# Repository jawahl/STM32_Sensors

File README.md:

# STM32_Sensors
Designing a board around the STM32F407 microcontroller to interface with GPS Rx, IMU, Temp sensors. 
Goal is to implement data logging & data filtering (dsp/control algorithms) in C/C++ firmware. 
Would also like to familiarize myself with freeRTOS.

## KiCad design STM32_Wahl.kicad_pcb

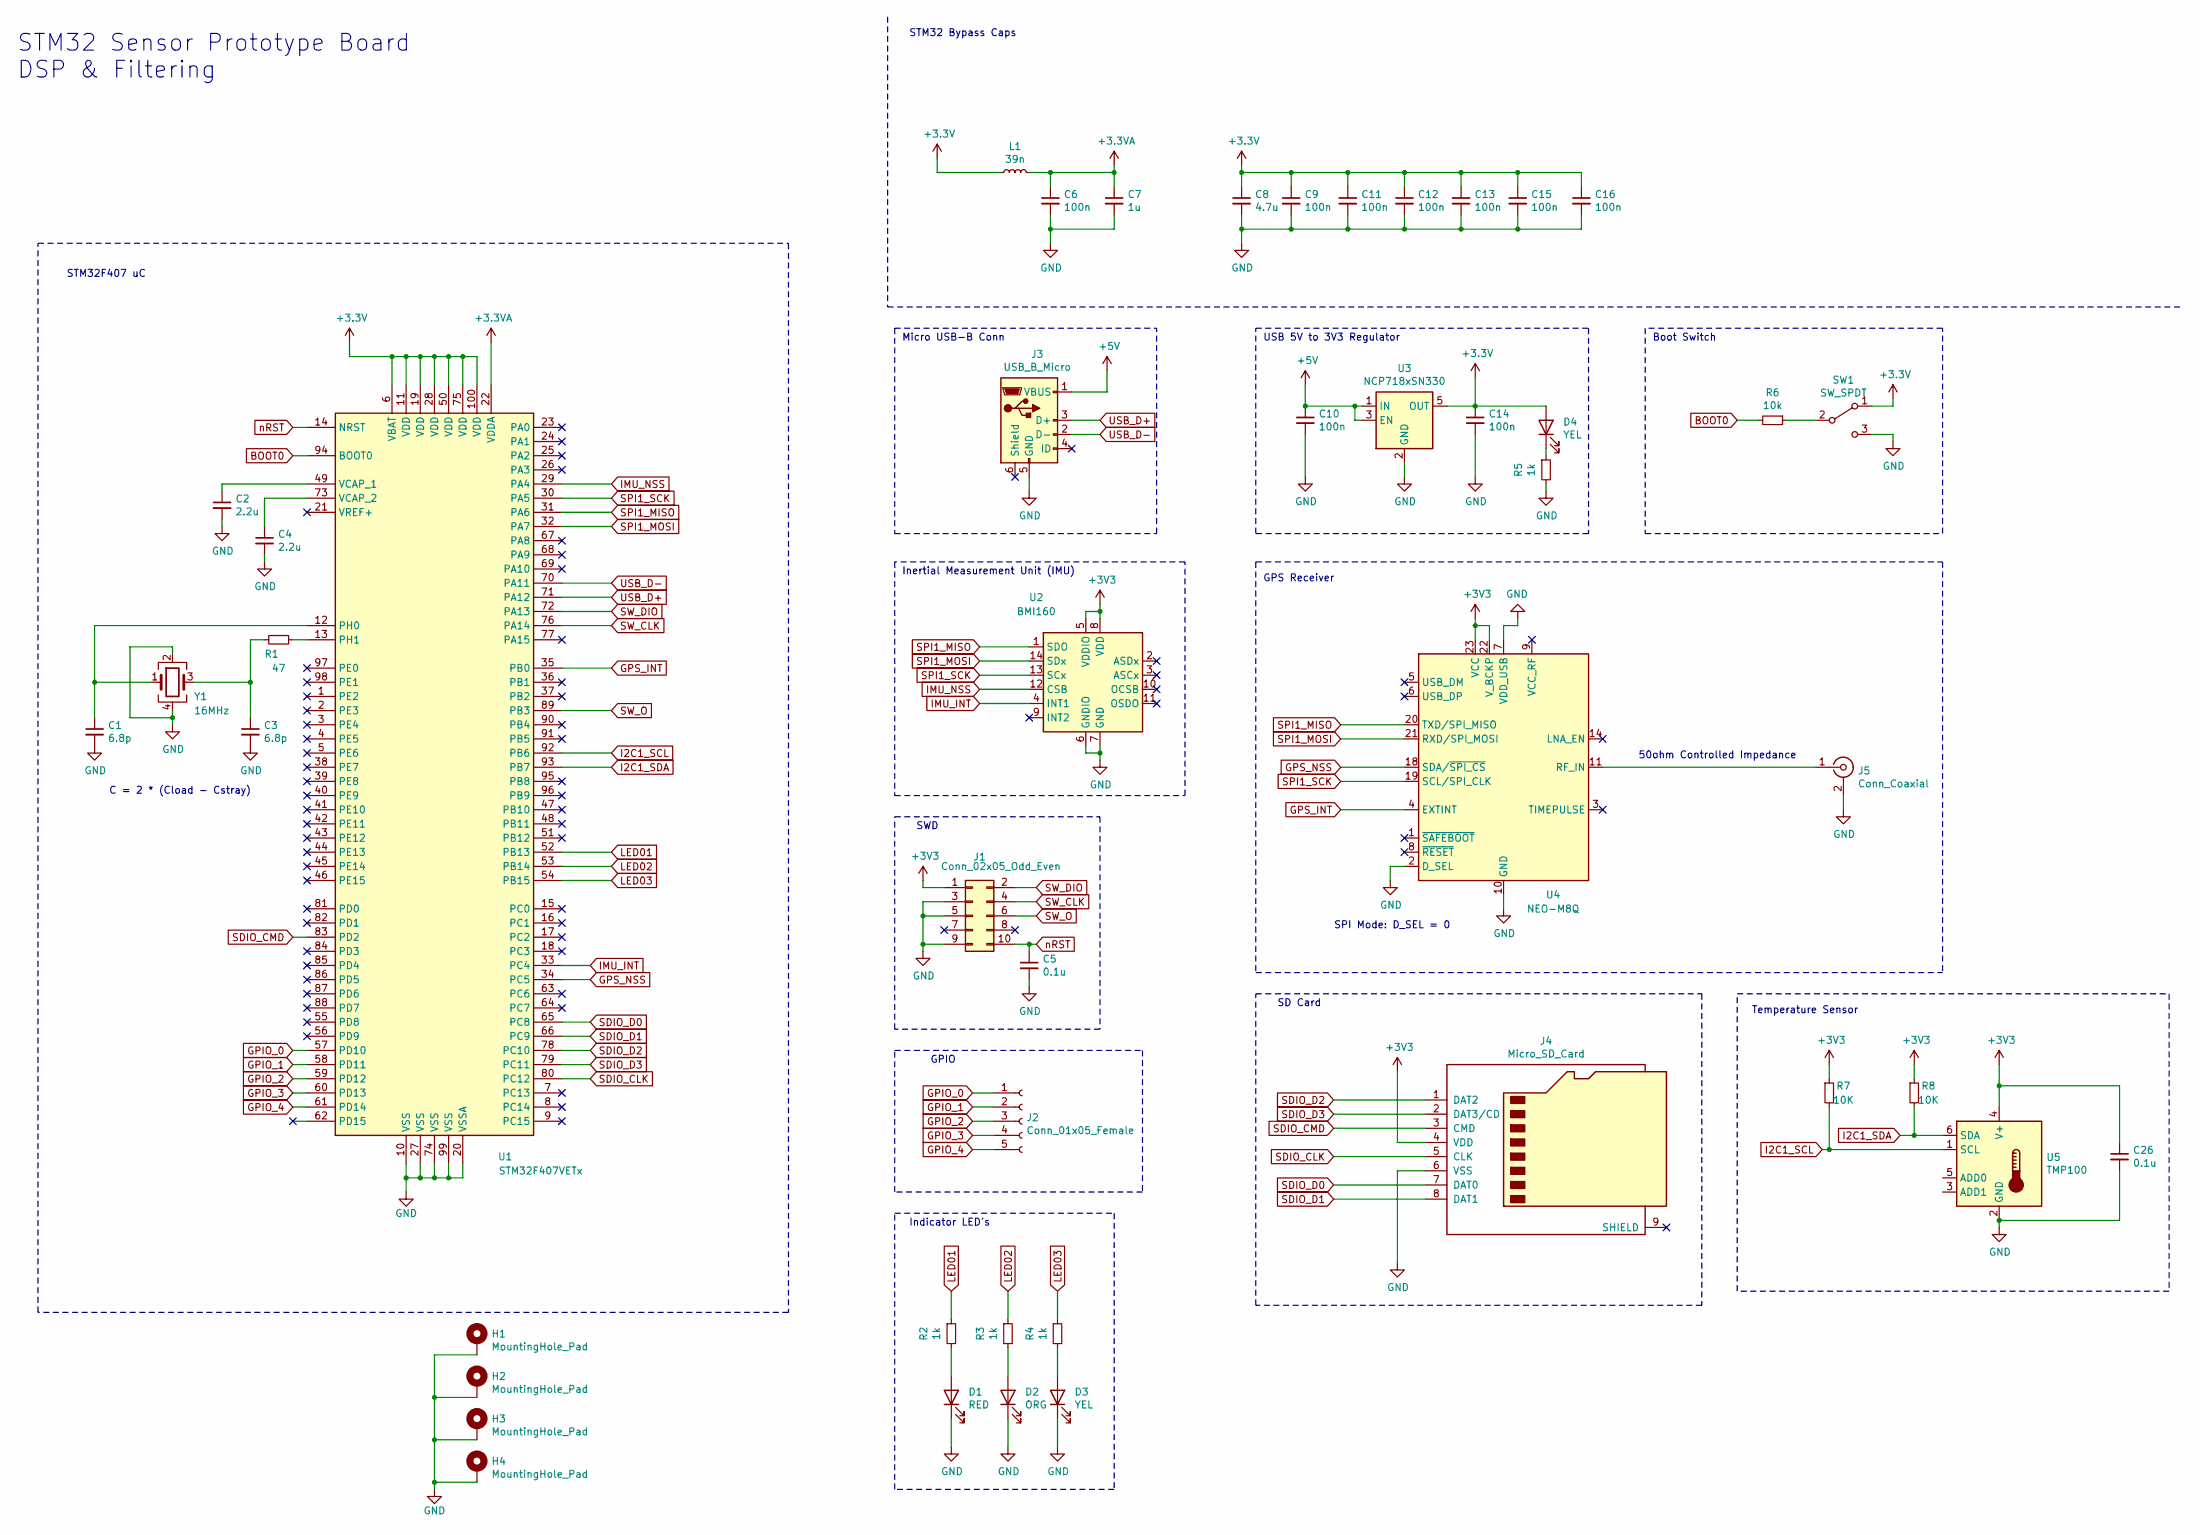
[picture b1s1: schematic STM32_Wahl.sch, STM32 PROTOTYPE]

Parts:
C1, C3: 6.8p; C_0402_1005Metric
C2, C4: 2.2u; C_0603_1608Metric
C5, C26: 0.1u; C_0603_1608Metric
C6: 100n; C_0603_1608Metric
C7: 1u; C_0603_1608Metric
C8: 4.7u; C_0603_1608Metric
C9, C10, C11, C12, C13, C14, C15, C16: 100n; C_0402_1005Metric
D1: RED; LED_0603_1608Metric
D2: ORG; LED_0603_1608Metric
D3, D4: YEL; LED_0603_1608Metric
H1, H2, H3, H4: MountingHole_Pad; MountingHole_4.3mm_M4_Pad_Via
J1: Conn_02x05_Odd_Even; PinHeader_2x05_P1.27mm_Vertical_SMD
J2: Conn_01x05_Female; PinSocket_1x05_P1.27mm_Vertical_SMD_Pin1Left
J3: USB_B_Micro; USB_Micro-B_Amphenol_10118194_Horizontal
J4: Micro_SD_Card; microSD_HC_Molex_104031-0811
J5: Conn_Coaxial; SMA_Amphenol_132291_Vertical
L1: 39n; L_0402_1005Metric
R1: 47; R_0402_1005Metric
R2, R3, R4, R5: 1k; R_0603_1608Metric
R6: 10k; R_0402_1005Metric
R7, R8: 10K; R_0402_1005Metric
SW1: SW_SPDT; SW_SPDT_PCM12
U1: STM32F407VETx; LQFP-100_14x14mm_P0.5mm
U2: BMI160; Bosch_LGA-14_3x2.5mm_P0.5mm
U3: NCP718xSN330; SOT-23-5
U4: NEO-M8Q; ublox_NEO
U5: TMP100; SOT-23-6
Y1: 16MHz; Crystal_SMD_3225-4Pin_3.2x2.5mm

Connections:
+3.3VA: C6.1, C7.1, L1.2, U1.22 (VDDA)
+5V: C10.1, J3.1 (VBUS), U3.1 (IN), U3.3 (EN)
BOOT0: R6.2, U1.94 (BOOT0)
GND: C1.2, C2.2, C3.2, C4.2, C5.2, C6.2, C7.2, C8.2, C9.2, C10.2, C11.2, C12.2, C13.2, C14.2, C15.2, C16.2, C26.2, D1.1 (K), D2.1 (K), D3.1 (K), H1.1, H2.1, H3.1, H4.1, J1.3, J1.5, J1.9, J3.5 (GND), J4.6 (VSS), J5.2 (Ext), R5.2, SW1.3 (C), U1.10 (VSS), U1.20 (VSSA), U1.27 (VSS), U1.74 (VSS), U1.99 (VSS), U2.6 (GNDIO), U2.7 (GND), U3.2 (GND), U4.2 (D_SEL), U4.7 (VDD_USB), U4.10 (GND), U4.12 (GND), U4.13 (GND), U4.24 (GND), U5.2 (GND), Y1.2, Y1.4
GPIO_0: J2.1, U1.57 (PD10)
GPIO_1: J2.2, U1.58 (PD11)
GPIO_2: J2.3, U1.59 (PD12)
GPIO_3: J2.4, U1.60 (PD13)
GPIO_4: J2.5, U1.61 (PD14)
GPS_INT: U1.35 (PB0), U4.4 (EXTINT)
GPS_NSS: U1.34 (PC5), U4.18 (SDA/~SPI_CS)
I2C1_SCL: R7.2, U1.92 (PB6), U5.1 (SCL)
I2C1_SDA: R8.2, U1.93 (PB7), U5.6 (SDA)
IMU_INT: U1.33 (PC4), U2.4 (INT1)
IMU_NSS: U1.29 (PA4), U2.12 (CSB)
LED01: R2.1, U1.52 (PB13)
LED02: R3.1, U1.53 (PB14)
LED03: R4.1, U1.54 (PB15)
unnamed: C1.1, U1.12 (PH0), Y1.1
unnamed: C2.1, U1.49 (VCAP_1)
unnamed: C3.1, R1.2, Y1.3
unnamed: C4.1, U1.73 (VCAP_2)
unnamed: D1.2 (A), R2.2
unnamed: D2.2 (A), R3.2
unnamed: D3.2 (A), R4.2
unnamed: D4.1 (K), R5.1
unnamed: J5.1 (In), U4.11 (RF_IN)
unnamed: R1.1, U1.13 (PH1)
unnamed: R6.1, SW1.2 (B)
SDIO_CLK: J4.5 (CLK), U1.80 (PC12)
SDIO_CMD: J4.3 (CMD), U1.83 (PD2)
SDIO_D0: J4.7 (DAT0), U1.65 (PC8)
SDIO_D1: J4.8 (DAT1), U1.66 (PC9)
SDIO_D2: J4.1 (DAT2), U1.78 (PC10)
SDIO_D3: J4.2 (DAT3/CD), U1.79 (PC11)
SPI1_MISO: U1.31 (PA6), U2.1 (SDO), U4.20 (TXD/SPI_MISO)
SPI1_MOSI: U1.32 (PA7), U2.14 (SDx), U4.21 (RXD/SPI_MOSI)
SPI1_SCK: U1.30 (PA5), U2.13 (SCx), U4.19 (SCL/SPI_CLK)
SW_CLK: J1.4, U1.76 (PA14)
SW_DIO: J1.2, U1.72 (PA13)
SW_O: J1.6, U1.89 (PB3)
USB_D+: J3.3 (D+), U1.71 (PA12)
USB_D-: J3.2 (D-), U1.70 (PA11)
nRST: C5.1, J1.10, U1.14 (NRST)

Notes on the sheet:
Inertial Measurement Unit (IMU)
GPS Receiver
SPI Mode: D_SEL = 0
50ohm Controlled Impedance
Boot Switch
USB 5V to 3V3 Regulator
Micro USB-B Conn
STM32 Bypass Caps
STM32 Sensor Prototype Board DSP & Filtering
C = 2 * (Cload - Cstray)
SWD
GPIO
SD Card
Indicator LED's
Temperature Sensor
STM32F407 uC

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
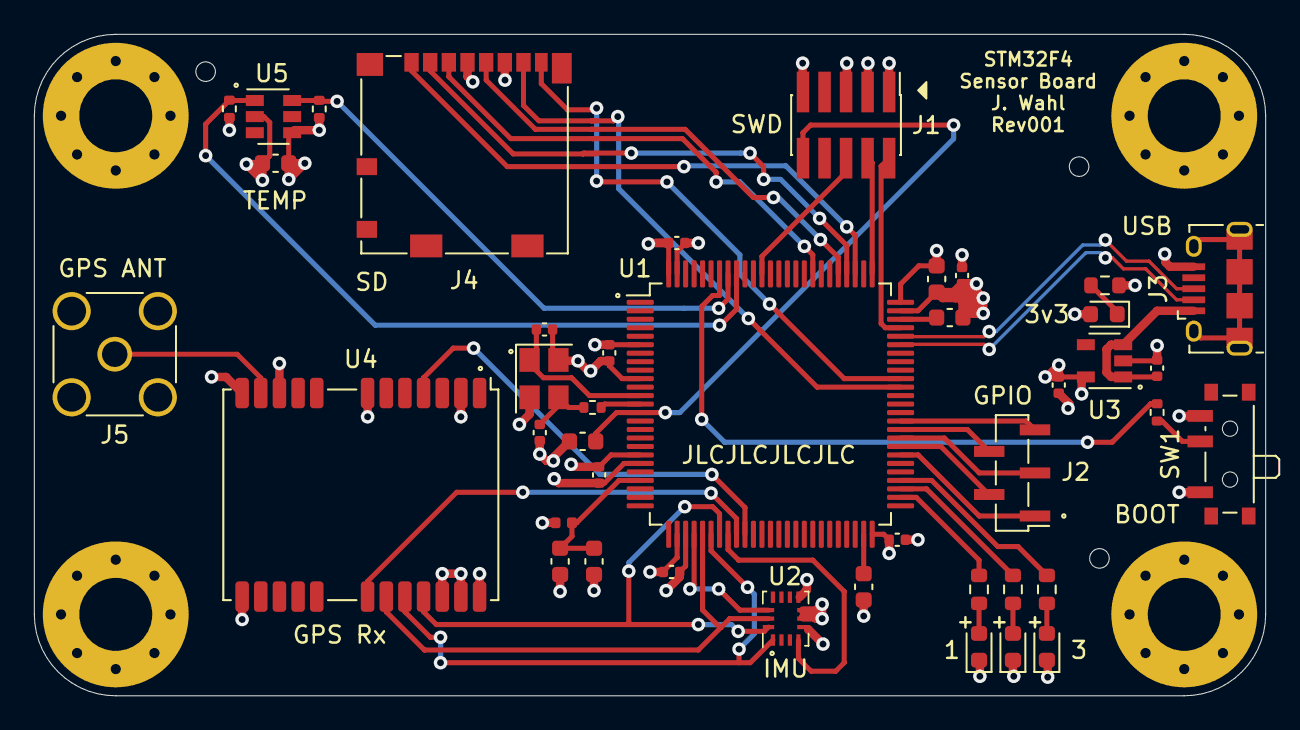
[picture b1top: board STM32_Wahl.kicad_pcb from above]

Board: 4 copper layers, 72.6 x 39.0 mm, 46 parts (0 on the bottom side), 45 nets.

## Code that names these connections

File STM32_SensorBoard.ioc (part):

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Mcu.Name=STM32F407V(E-G)Tx
Mcu.Package=LQFP100
Mcu.UserName=STM32F407VETx
PA11.Mode=Device_Only
PA11.Signal=USB_OTG_FS_DM
PA12.Mode=Device_Only
PA12.Signal=USB_OTG_FS_DP
PA13.Mode=Trace_Asynchronous_SW
PA13.Signal=SYS_JTMS-SWDIO
PA14.Mode=Trace_Asynchronous_SW
PA14.Signal=SYS_JTCK-SWCLK
PA4.GPIOParameters=PinState,GPIO_Label
PA4.GPIO_Label=IMU_NSS
PA4.PinState=GPIO_PIN_SET
PA4.Signal=GPIO_Output
PA5.Mode=Full_Duplex_Master
PA5.Signal=SPI1_SCK
PA6.Mode=Full_Duplex_Master
PA6.Signal=SPI1_MISO
PA7.Mode=Full_Duplex_Master
PA7.Signal=SPI1_MOSI
PB0.GPIOParameters=GPIO_Label
PB0.GPIO_Label=GPS_INT
PB0.Signal=GPXTI0
PB13.GPIOParameters=GPIO_Label
PB13.GPIO_Label=LED01
PB13.Signal=GPIO_Output
PB14.GPIOParameters=GPIO_Label
PB14.GPIO_Label=LED02
PB14.Signal=GPIO_Output
PB15.GPIOParameters=GPIO_Label
PB15.GPIO_Label=LED03
PB15.Signal=GPIO_Output
PB3.Mode=Trace_Asynchronous_SW
PB3.Signal=SYS_JTDO-SWO
PB6.Mode=I2C
PB6.Signal=I2C1_SCL
PB7.Mode=I2C
PB7.Signal=I2C1_SDA
PC10.Mode=SD_4_bits_Wide_bus
PC10.Signal=SDIO_D2
PC11.Mode=SD_4_bits_Wide_bus
PC11.Signal=SDIO_D3
PC12.Mode=SD_4_bits_Wide_bus
PC12.Signal=SDIO_CK
PC4.GPIOParameters=GPIO_Label
PC4.GPIO_Label=IMU_INT
PC4.Signal=GPXTI4
PC5.GPIOParameters=GPIO_Label
PC5.GPIO_Label=GPS_NSS
PC5.Signal=GPIO_Output
PC8.Mode=SD_4_bits_Wide_bus
PC8.Signal=SDIO_D0
PC9.Mode=SD_4_bits_Wide_bus
PC9.Signal=SDIO_D1
PD10.GPIOParameters=GPIO_Label
PD10.GPIO_Label=GPIO_4
PD10.Signal=GPIO_Output
PD11.GPIOParameters=GPIO_Label
PD11.GPIO_Label=GPIO_3
PD11.Signal=GPIO_Output
PD12.GPIOParameters=GPIO_Label
PD12.GPIO_Label=GPIO_2
PD12.Signal=GPIO_Output
PD13.GPIOParameters=GPIO_Label
PD13.GPIO_Label=GPIO_1
PD13.Signal=GPIO_Output
PD14.GPIOParameters=GPIO_Label
PD14.GPIO_Label=GPIO_0
PD14.Signal=GPIO_Output
PD2.Mode=SD_4_bits_Wide_bus
PD2.Signal=SDIO_CMD
PE9.Signal=S_TIM1_CH1
PH0-OSC_IN.Mode=HSE-External-Oscillator
PH0-OSC_IN.Signal=RCC_OSC_IN
PH1-OSC_OUT.Mode=HSE-External-Oscillator
PH1-OSC_OUT.Signal=RCC_OSC_OUT
RCC.HSE_VALUE=16000000
RCC.SYSCLKFreq_VALUE=168000000
RCC.SYSCLKSource=RCC_SYSCLKSOURCE_PLLCLK
board=custom

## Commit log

2021-09-06 initial commit
    adds schematic, brd, netlist
2021-09-06 add pcb jpeg
